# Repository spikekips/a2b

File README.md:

<!--<div align="center">-->

# A2B - Audio & Power to Breadboard Interface

**A convenient open-source hardware interface board for integrating 1/4" audio and 9V DC power with breadboard projects.**

<!-- </div> -->

## Overview

The `a2b` project provides an open-source hardware solution for seamlessly integrating common audio and power sources directly into your breadboard experiments. This board is designed to take standard 1/4" audio input jacks and a 9V DC power input, breaking them out into breadboard-friendly header pins.

Whether you're prototyping audio circuits, experimenting with effects pedals, or simply need a stable power supply for your digital or analog breadboard designs, `a2b` simplifies the connection process, reducing clutter and the need for awkward jumper wire setups. It's ideal for hobbyists, educators, and professional engineers working on audio electronics and general prototyping.

## Features

-   **1/4" Audio Input Jacks**: Standard stereo 1/4" (6.35mm) jacks for easy connection of audio sources.
-   **9V DC Power Input**: A dedicated 9V DC jack for powering the board and providing a stable voltage to your breadboard.
-   **Breadboard-Friendly Output**: Standard 0.1" (2.54mm) header pins for direct connection into a breadboard.
-   **Comprehensive KiCad Design**: Full schematic and PCB layout files provided for transparency, customization, and learning.
-   **Ready-to-Manufacture Files**: Includes Gerber files and a Bill of Materials (BOM) for easy PCB fabrication and component sourcing.
-   **Open Hardware**: Licensed under CERN-OHL-S-2.0, promoting collaboration and reuse.

## Renders & Photos

<!-- TODO: Add actual 3D renders or photos of the physical PCB/assembled board here. -->
<!-- Example:

_3D Render: Top View of the a2b board_

_3D Render: Bottom View with component outlines_

_Photo: An assembled a2b board connected to a breadboard_
-->

## Tech Stack

**ECAD Software:**

Ver. 10.0 or greater

## Getting Started (Building & Ordering)

This project is hardware-focused, meaning "getting started" involves either reviewing the design files in KiCad or preparing the files for manufacturing.

### Prerequisites

-   **KiCad EDA Suite**: To view, modify, or export the design files. You can download it from [kicad.org](https://www.kicad.org/).

### Design Files

1.  **Clone the repository**:
    ```bash
    git clone https://github.com/spikekips/a2b.git
    cd a2b
    ```

2.  **Open in KiCad**:
    *   Launch KiCad.
    *   Open the project file `a2b.kicad_pro`.
    *   You can then open `a2b.kicad_sch` for the schematic and `a2b.kicad_pcb` for the PCB layout.

### Manufacturing Your Own Board

The repository includes all necessary files to order the `a2b` PCB and assemble it yourself.

1.  **Gerber Files**:
    *   The `gerber.zip` archive contains all the necessary files for PCB fabrication (e.g., copper layers, solder mask, silkscreen, drill files).
    *   You can upload this `.zip` file directly to most PCB manufacturers (e.g., JLCPCB, PCBWay, OSH Park).
    *   An unzipped `gerber` directory is also provided for review.

2.  **Bill of Materials (BOM)**:
    *   The `bom/` directory should contain the list of electronic components required for assembly.
    <!--*-->   <!-- TODO: Confirm the exact format and location of the BOM file (e.g., bom/a2b_bom.csv) and provide instructions. -->
    *   You can use this BOM to source components from distributors like Digi-Key, Mouser, or LCSC.

3.  **Assembly**:
    *   Once you receive the PCBs and components, assemble them by soldering the components onto the board according to the schematic (`a2b.kicad_sch`) and the PCB layout (`a2b.kicad_pcb`).
    *   Refer to the silkscreen markings on the PCB for component placement.

<!--
## Project Structure

```
a2b/
├── .history/               # Internal historical data (can be ignored)
├── My_Library/             # Custom KiCad footprints or symbols
├── a2b-backups/            # Backups of KiCad design files
├── a2b.kicad_pcb           # Main PCB layout file
├── a2b.kicad_prl           # KiCad project local settings
├── a2b.kicad_pro           # Main KiCad project file
├── a2b.kicad_sch           # Main schematic file
├── a2b.zip                 # Archive of the project (or specific output)
├── bom/                    # Directory for Bill of Materials files
├── customHeaders.bak       # Backup file, likely related to KiCad headers
├── fp-lib-table            # KiCad footprint library table configuration
├── gerber/                 # Unzipped Gerber files for PCB manufacturing
├── gerber.zip              # Zipped Gerber files for PCB manufacturing
├── license.md              # CERN Open Hardware Licence file
├── README.md               # This README file
└── sym-lib-table           # KiCad symbol library table configuration
```
-->

## Usage & Pinout

The a2b board is designed to be plugged directly into a breadboard. The output header provides audio input and output along with 9V in.

T R S is your audio signal if you plug in a 1/4" jack into the plugs you can output the signal to your bread board or jump them to make a passthrough.

Your voltage outputs are determined by the polarity of your power supply. Wether or not you have a positive or negative center pin on your powersupply is determined by the LEDs. Determine the polarity from which light is on. The polarity symbol on the lit up side will be your reference for your Vout.

<!-- TODO: Add a clear diagram or table explaining the pinout of the breadboard headers and how to connect audio/power inputs. -->
<!-- Example:
### Connecting to a Breadboard

The `a2b` board is designed to be plugged directly into a breadboard. The output header provides:

| Pin | Description            |

|-----|------------------------|

| VCC | 9V DC regulated output |

| GND | Ground                 |

| L_A | Left Audio Channel     |

| R_A | Right Audio Channel    |

Connect your 1/4" audio source to the input jacks and a 9V DC power supply to the barrel jack.
-->

## Contributing

This is an open-source hardware project, and we welcome contributions! If you have suggestions for improvements, find errors in the design, or want to contribute to documentation:

1.  **Fork the repository.**
2.  **Create your feature branch:** `git checkout -b feature/AmazingFeature`
3.  **Make your changes.**
4.  **Commit your changes:** `git commit -m 'Add some AmazingFeature'`
5.  **Push to the branch:** `git push origin feature/AmazingFeature`
6.  **Open a Pull Request.**

Please ensure your contributions adhere to the [CERN Open Hardware Licence Version 2 - Strongly Reciprocal](license.md).

### Development Setup for Contributors
To contribute to the design files, you'll need the KiCad( > 10.0) EDA Suite installed. After cloning, simply open the `a2b.kicad_pro` file in KiCad.

## License

This project is licensed under the [CERN Open Hardware Licence Version 2 - Strongly Reciprocal](license.md) - see the `license.md` file for full details.

## Acknowledgments

-   **KiCad Community**: For providing an excellent open-source ECAD suite that makes projects like this possible.

## Support & Contact

-   Issues: [GitHub Issues](https://github.com/spikekips/a2b/issues)
-   Feel free to reach out to the repository owner, [spikekips](https://github.com/spikekips), for questions or support.

---

<div align="center">

**Star this repo if you find it helpful!**

Made by me, [spikekips](https://github.com/spikekips)

</div>

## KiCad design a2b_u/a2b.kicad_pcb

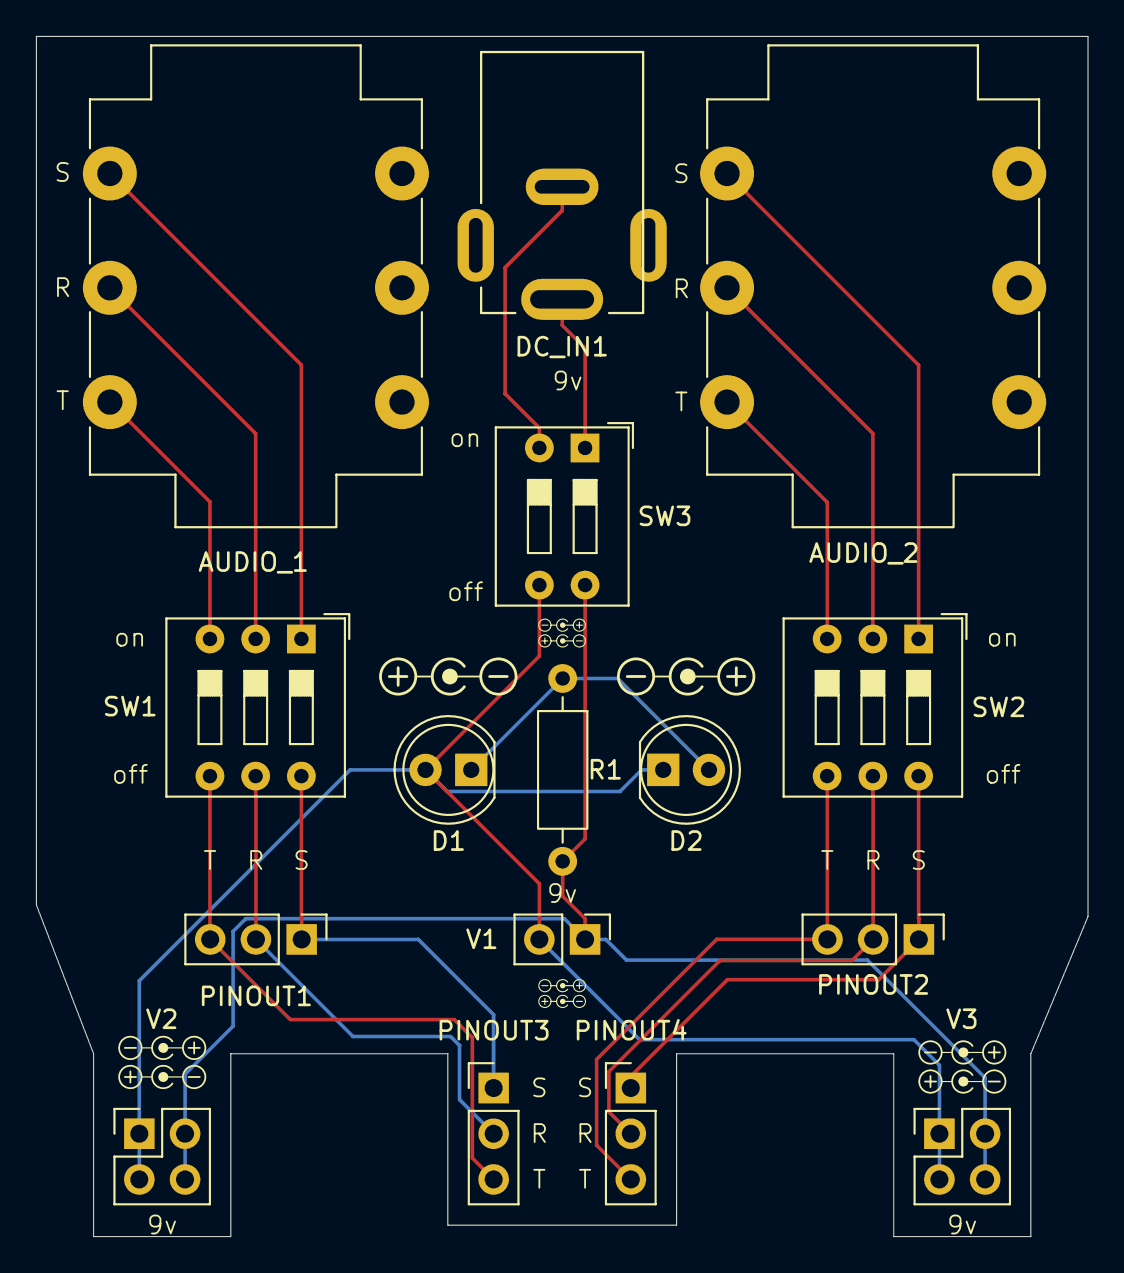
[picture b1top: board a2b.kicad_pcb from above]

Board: 2 copper layers, 58.4 x 66.7 mm, 16 parts (0 on the bottom side), 17 nets.

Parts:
AUDIO_1, AUDIO_2: NMJ6HCD2; Jack_6.35mm_Neutrik_NMJ6HCD2_Horizontal
D1, D2: LED; LED_D5.0mm
DC_IN1: RAPC722X; SWITCHCRAFT_RAPC722X
PINOUT1, PINOUT2, PINOUT3, PINOUT4: PinHeader_1x03_P2.54mm_Vertical
R1: 1k; R_Axial_DIN0207_L6.3mm_D2.5mm_P10.16mm_Horizontal
SW1, SW2: SW_DIP_x03; SW_DIP_SPSTx03_Slide_9.78x9.8mm_W7.62mm_P2.54mm
SW3: SW_DIP_x02; SW_DIP_SPSTx02_Slide_9.78x7.26mm_W7.62mm_P2.54mm
V1: PinHeader_1x02_P2.54mm_Vertical
V2, V3: PinHeader_2x02_P2.54mm_Vertical

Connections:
/Net-(PINOUT2-Pad2): PINOUT2.2, PINOUT4.2, SW2.5
/Net-(PINOUT2-Pad3): PINOUT2.3, PINOUT4.3, SW2.4
unnamed: AUDIO_1.R, SW1.2
unnamed: AUDIO_1.S, SW1.1
unnamed: AUDIO_1.T, SW1.3
unnamed: AUDIO_2.R, SW2.2
unnamed: AUDIO_2.S, SW2.1
unnamed: AUDIO_2.T, SW2.3
unnamed: D1.2 (A), D2.1 (K), SW3.3, V1.2, V2.1, V2.3, V3.1, V3.3
unnamed: D1.1 (K), D2.2 (A), R1.1
unnamed: DC_IN1.PIN, SW3.1
unnamed: DC_IN1.SLEEVE, SW3.2
unnamed: PINOUT1.1, PINOUT3.1, SW1.6
unnamed: PINOUT1.2, PINOUT3.2, SW1.5
unnamed: PINOUT1.3, PINOUT3.3, SW1.4
unnamed: PINOUT2.1, PINOUT4.1, SW2.6
unnamed: R1.2, SW3.4, V1.1, V2.2, V2.4, V3.2, V3.4

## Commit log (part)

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2026-05-03 UPDATE PCB
2026-05-03 ASDF
2026-05-04 update pcb and schematic
2026-05-05 update pcb silkscreens
2026-05-07 add BOM
2026-05-11 swap to dip switches Signed-off-by: MrMentalFlower <samuelejpike@gmail.com>
2026-05-11 update dips switches and silk screen
2026-05-13 swap switch
2026-05-13 update BOM
2026-05-19 Change 2 switch dip switches from 2 switch to 3 switch so you can control the ground.
2026-05-19 Swap + & - on board silkscreen and added extra + & - prongs.
2026-05-26 update pcb components and routing
2026-05-28 Sent to get printed
2026-06-11 added silkscreen
2026-06-15 updated silkscreen
2026-06-16 add 3d models
2026-06-17 update some 3d models and graphics
2026-06-17 Remake gerber and archive
2026-06-17 flip pins
2026-06-18 add U_D
2026-06-18 fixing board
2026-06-18 update git
2026-06-18 Verification
2026-06-18 Update license
2026-06-18 sync board
2026-06-18 update gerber and project zip
2026-06-18 Update gerber and bom
2026-06-18 Generate BOM
2026-06-18 finalize update
2026-06-19 Change trace routing
2026-06-19 update traces
2026-06-19 Update README.md
    update photos
2026-06-22 managing files
2026-06-22 manage files
